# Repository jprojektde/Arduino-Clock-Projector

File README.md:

# Arduino-Clock-Projector  
A simple little projector module for your DIY alarm clock 🕒✨

Building an alarm clock **with a real wall projector** is surprisingly hard.  
Until now there wasn’t really an easy way to just *buy a small module* that can project the time cleanly.

So I went looking and found this **cheap LED projector lamp on AliExpress**:  
https://de.aliexpress.com/item/1005009155662454.html  

It’s super affordable, but it also has a few downsides:

- It’s a **7-segment display**
- You only get **3 full digits**
- The first digit is basically a “1” made from only **two segments**
- Plus the **":"** in the middle

That said — the important part is:  
✅ We only need the **LCD**, the **rubber contact piece**, and the **lens** from the projector.

---

## Pictures

Here are a few pictures from the project:

---

## What’s in this project?

I designed a custom PCB using the **HT1621 LCD driver**, and the rest of the build is done with **3D printed parts**.  
All required files are included in this repository.

For a nicer final look, you can also add a small glass plate (20×1.5mm) from AliExpress:  
https://de.aliexpress.com/item/1005003692263992.html  

---

## Testing it

I also included a small **Arduino test sketch** so you can try it immediately.

**Basic setup:**
- Connect the module to your Arduino
- Add a small resistor for the LED
- Power it up and enjoy the magic 😄

If the image isn’t sharp, just **twist the lens holder** until the projection is in focus.

From my experience, the LED works best in darker rooms and projects clearly for about **3–4 meters**.

---

## LED recommendation (important!)

It’s **really important** to use an LED with a **15° viewing angle**, otherwise the projection will look weak or blurry.

These LEDs work great (I used them myself):

**Green:**  
https://www.reichelt.de/de/de/shop/produkt/led_5_mm_bedrahtet_gruen_43300_mcd_15_-230982  

**Classic Red:**  
https://www.reichelt.de/de/de/shop/produkt/led_5mm_bedrahtet_rot_20000_mcd_15_-361605?nbc=1  

---

Have fun testing and tinkering! 😄🔧

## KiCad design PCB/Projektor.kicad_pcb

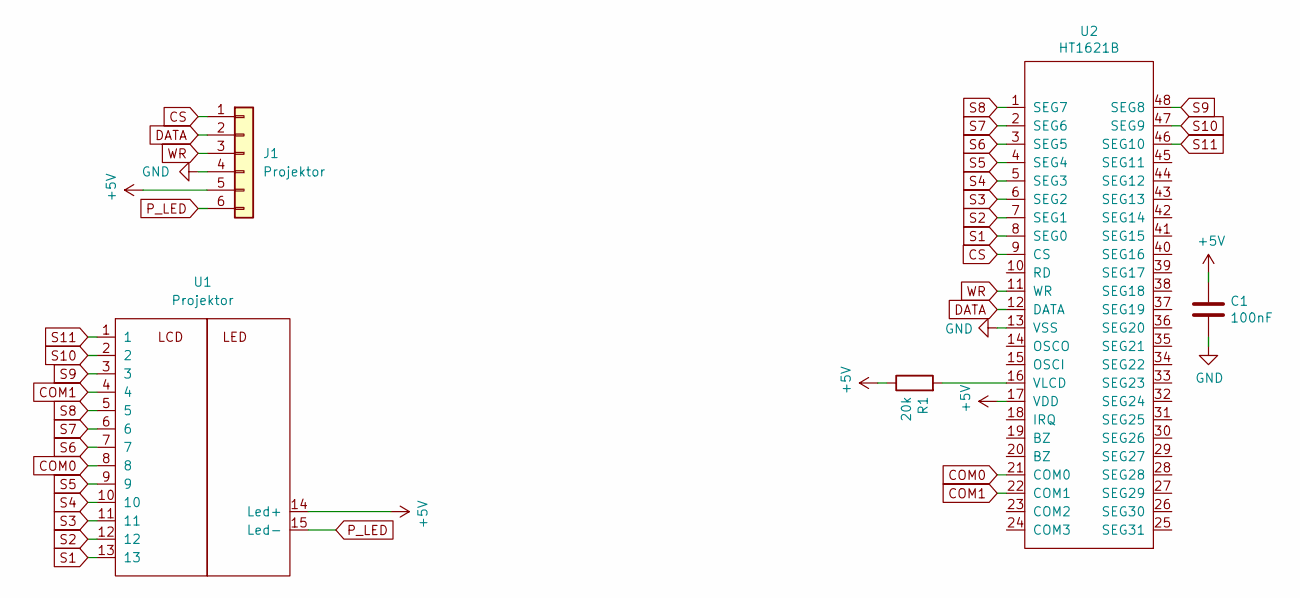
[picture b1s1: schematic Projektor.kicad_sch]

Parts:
C1: 100nF; C_0603_1608Metric
J1: Projektor; Molex_PicoBlade_53047-0610_1x06_P1.25mm_Vertical
R1: 20k; R_0603_1608Metric
U1: Projektor; Projektor_Controlliert
U2: HT1621B; SSOP-48_7.5x15.9mm_P0.635mm

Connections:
+5V: C1.1, J1.5, R1.1, U1.14 (Led+), U2.17 (VDD)
COM0: U1.8, U2.21 (COM0)
COM1: U1.4, U2.22 (COM1)
CS: J1.1, U2.9 (CS)
DATA: J1.2, U2.12 (DATA)
GND: C1.2, J1.4, U2.13 (VSS)
unnamed: R1.2, U2.16 (VLCD)
P_LED: J1.6, U1.15 (Led-)
S1: U1.13, U2.8 (SEG0)
S2: U1.12, U2.7 (SEG1)
S3: U1.11, U2.6 (SEG2)
S4: U1.10, U2.5 (SEG3)
S5: U1.9, U2.4 (SEG4)
S6: U1.7, U2.3 (SEG5)
S7: U1.6, U2.2 (SEG6)
S8: U1.5, U2.1 (SEG7)
S9: U1.3, U2.48 (SEG8)
S10: U1.2, U2.47 (SEG9)
S11: U1.1, U2.46 (SEG10)
WR: J1.3, U2.11 (WR)

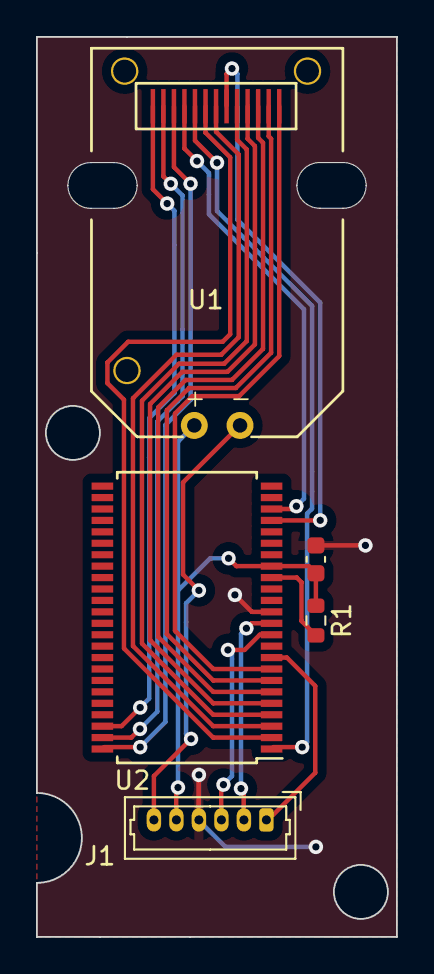
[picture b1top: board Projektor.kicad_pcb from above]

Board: 2 copper layers, 20.0 x 50.0 mm, 5 parts (0 on the bottom side), 20 nets.

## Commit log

2026-01-13 Add Project Files
2026-01-13 Add Project Pictures
